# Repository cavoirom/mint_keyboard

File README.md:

# Mint Keyboard

Mint is an attempt to build 4x12 ortholinear keyboard with ***Weact STM32F411CEU6 Black Pill***. This repository include PCB design, plate design that anyone can build a Mint for themselves.

## Bill of materials

| Name                                 | Quantities | Ref | Description                                                |
|--------------------------------------|------------|-----|------------------------------------------------------------|
| Weact STM32F411CEU6 Black Pill       | 1          |     | Keyboard controller                                        |
| 1N4148 Diode                         | 47         |     |                                                            |
| Kailh Hotswap Socket                 | 44         |     |                                                            |
| Mill-Max sockets 0305                | 6          |     | 3 sockets above the controller could not use Kailh socket. |

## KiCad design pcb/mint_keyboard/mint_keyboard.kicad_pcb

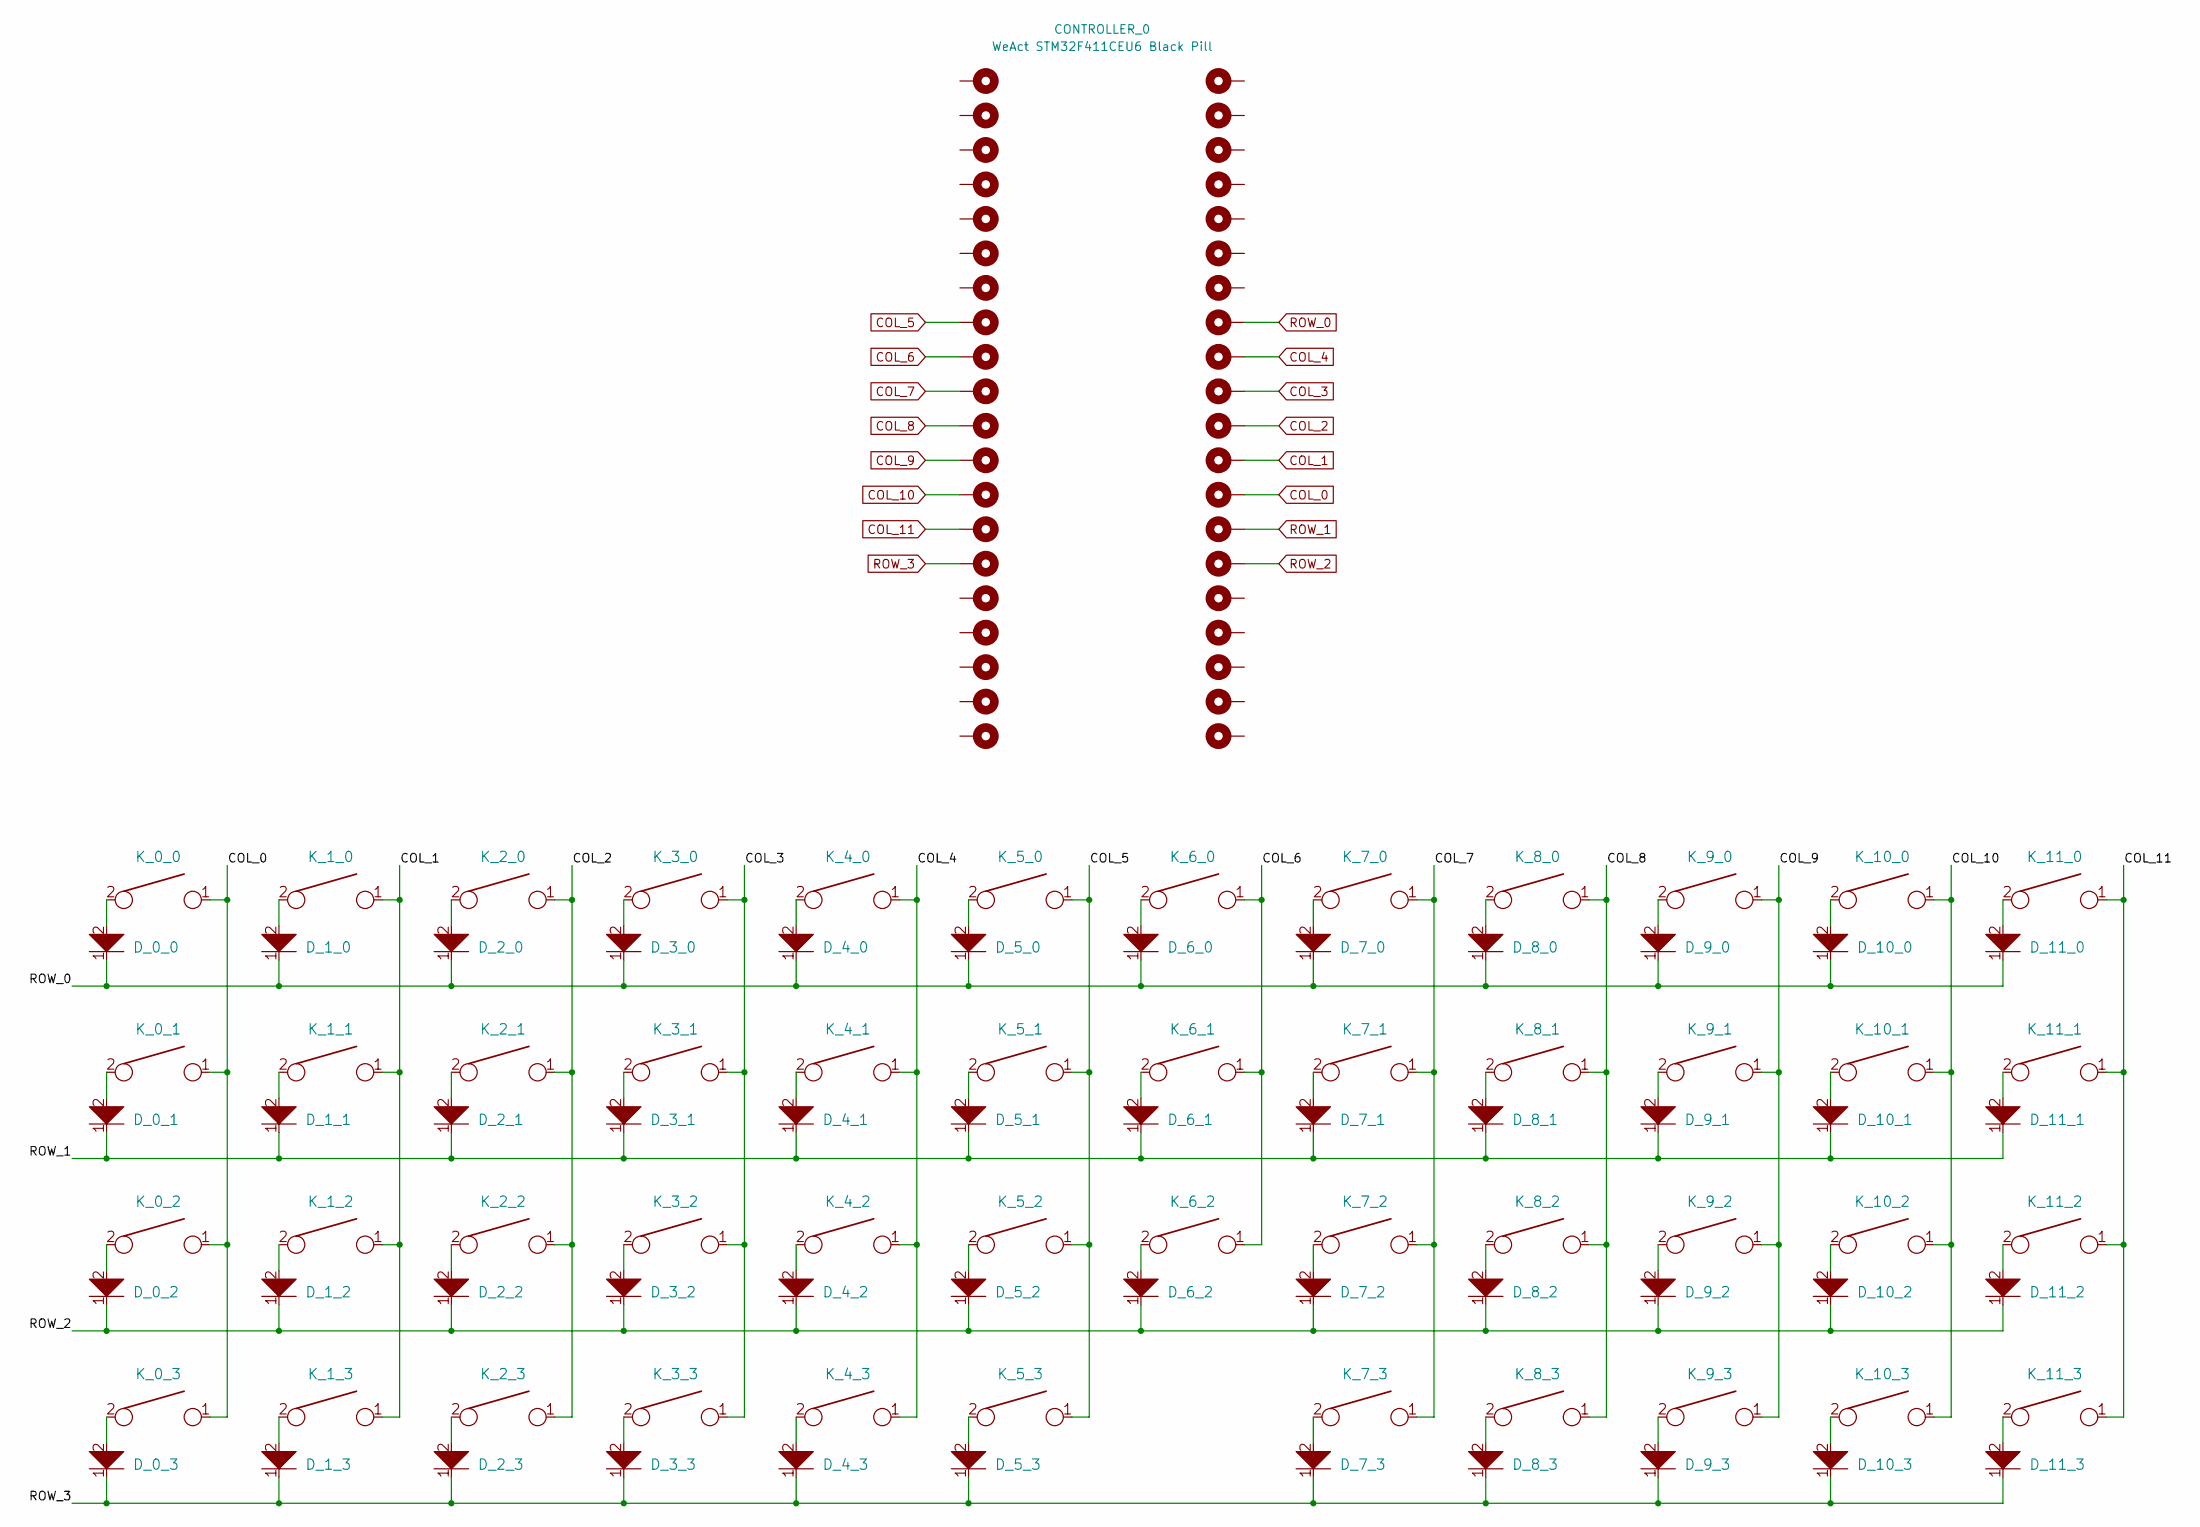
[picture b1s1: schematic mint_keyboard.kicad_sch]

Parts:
CONTROLLER_0: WeAct STM32F411CEU6 Black Pill; WeAct_STM32F411CEU6_Black_Pill_v3
D_0_0, D_0_1, D_0_2, D_0_3, D_1_0, D_1_1, D_1_2, D_1_3, D_2_0, D_2_1, D_2_2, D_2_3, D_3_0, D_3_1, D_3_2, D_3_3, D_4_0, D_4_1, D_4_2, D_4_3, D_5_0, D_5_1, D_5_2, D_5_3, D_6_0, D_6_1, D_6_2, D_7_0, D_7_1, D_7_2, D_7_3, D_8_0, D_8_1, D_8_2, D_8_3, D_9_0, D_9_1, D_9_2, D_9_3, D_10_0, D_10_1, D_10_2, D_10_3, D_11_0, D_11_1, D_11_2, D_11_3: D; D_DO-35_SOD27_P7.62mm_Horizontal
K_0_0: TAB; Kailh_socket_MX_padding
K_0_1, K_0_2, K_0_3, K_1_1, K_1_2, K_1_3, K_2_1, K_2_2, K_2_3, K_3_1, K_3_2, K_3_3, K_4_3, K_5_1, K_5_2, K_5_3, K_6_1, K_6_2, K_7_1, K_7_2, K_7_3, K_8_1, K_8_2, K_8_3, K_9_1, K_9_2, K_9_3, K_10_1, K_10_2, K_10_3, K_11_1, K_11_2, K_11_3: KEYSW; Kailh_socket_MX_padding
K_1_0: QUOTE; Kailh_socket_MX_padding
K_2_0: COMMA; Kailh_socket_MX_padding
K_3_0: PERIOD; Kailh_socket_MX_padding
K_4_0: P; SW_MX_padding
K_4_1, K_4_2: KEYSW; SW_MX_padding
K_5_0: Y; Kailh_socket_MX_padding
K_6_0: F; Kailh_socket_MX_padding
K_7_0: G; Kailh_socket_MX_padding
K_8_0: C; Kailh_socket_MX_padding
K_9_0: R; Kailh_socket_MX_padding
K_10_0: L; Kailh_socket_MX_padding
K_11_0: BACKSPACE; Kailh_socket_MX_padding

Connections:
COL_0: CONTROLLER_0.33 (A2), K_0_0.1, K_0_1.1, K_0_2.1, K_0_3.1
COL_1: CONTROLLER_0.32 (A3), K_1_0.1, K_1_1.1, K_1_2.1, K_1_3.1
COL_2: CONTROLLER_0.31 (A4), K_2_0.1, K_2_1.1, K_2_2.1, K_2_3.1
COL_3: CONTROLLER_0.30 (A5), K_3_0.1, K_3_1.1, K_3_2.1, K_3_3.1
COL_4: CONTROLLER_0.29 (A6), K_4_0.1, K_4_1.1, K_4_2.1, K_4_3.1
COL_5: CONTROLLER_0.8 (A11), K_5_0.1, K_5_1.1, K_5_2.1, K_5_3.1
COL_6: CONTROLLER_0.9 (A12), K_6_0.1, K_6_1.1, K_6_2.1
COL_7: CONTROLLER_0.10 (A15), K_7_0.1, K_7_1.1, K_7_2.1, K_7_3.1
COL_8: CONTROLLER_0.11 (B3), K_8_0.1, K_8_1.1, K_8_2.1, K_8_3.1
COL_9: CONTROLLER_0.12 (B4), K_9_0.1, K_9_1.1, K_9_2.1, K_9_3.1
COL_10: CONTROLLER_0.13 (B5), K_10_0.1, K_10_1.1, K_10_2.1, K_10_3.1
COL_11: CONTROLLER_0.14 (B6), K_11_0.1, K_11_1.1, K_11_2.1, K_11_3.1
unnamed: D_0_0.2, K_0_0.2
unnamed: D_0_1.2, K_0_1.2
unnamed: D_0_2.2, K_0_2.2
unnamed: D_0_3.2, K_0_3.2
unnamed: D_1_0.2, K_1_0.2
unnamed: D_1_1.2, K_1_1.2
unnamed: D_1_2.2, K_1_2.2
unnamed: D_1_3.2, K_1_3.2
unnamed: D_2_0.2, K_2_0.2
unnamed: D_2_1.2, K_2_1.2
unnamed: D_2_2.2, K_2_2.2
unnamed: D_2_3.2, K_2_3.2
unnamed: D_3_0.2, K_3_0.2
unnamed: D_3_1.2, K_3_1.2
unnamed: D_3_2.2, K_3_2.2
unnamed: D_3_3.2, K_3_3.2
unnamed: D_4_0.2, K_4_0.2
unnamed: D_4_1.2, K_4_1.2
unnamed: D_4_2.2, K_4_2.2
unnamed: D_4_3.2, K_4_3.2
unnamed: D_5_0.2, K_5_0.2
unnamed: D_5_1.2, K_5_1.2
unnamed: D_5_2.2, K_5_2.2
unnamed: D_5_3.2, K_5_3.2
unnamed: D_6_0.2, K_6_0.2
unnamed: D_6_1.2, K_6_1.2
unnamed: D_6_2.2, K_6_2.2
unnamed: D_7_0.2, K_7_0.2
unnamed: D_7_1.2, K_7_1.2
unnamed: D_7_2.2, K_7_2.2
unnamed: D_7_3.2, K_7_3.2
unnamed: D_8_0.2, K_8_0.2
unnamed: D_8_1.2, K_8_1.2
unnamed: D_8_2.2, K_8_2.2
unnamed: D_8_3.2, K_8_3.2
unnamed: D_9_0.2, K_9_0.2
unnamed: D_9_1.2, K_9_1.2
unnamed: D_9_2.2, K_9_2.2
unnamed: D_9_3.2, K_9_3.2
unnamed: D_10_0.2, K_10_0.2
unnamed: D_10_1.2, K_10_1.2
unnamed: D_10_2.2, K_10_2.2
unnamed: D_10_3.2, K_10_3.2
unnamed: D_11_0.2, K_11_0.2
unnamed: D_11_1.2, K_11_1.2
unnamed: D_11_2.2, K_11_2.2
unnamed: D_11_3.2, K_11_3.2
ROW_0: CONTROLLER_0.28 (A7), D_0_0.1, D_1_0.1, D_2_0.1, D_3_0.1, D_4_0.1, D_5_0.1, D_6_0.1, D_7_0.1, D_8_0.1, D_9_0.1, D_10_0.1, D_11_0.1
ROW_1: CONTROLLER_0.34 (A1), D_0_1.1, D_1_1.1, D_2_1.1, D_3_1.1, D_4_1.1, D_5_1.1, D_6_1.1, D_7_1.1, D_8_1.1, D_9_1.1, D_10_1.1, D_11_1.1
ROW_2: CONTROLLER_0.35 (A0), D_0_2.1, D_1_2.1, D_2_2.1, D_3_2.1, D_4_2.1, D_5_2.1, D_6_2.1, D_7_2.1, D_8_2.1, D_9_2.1, D_10_2.1, D_11_2.1
ROW_3: CONTROLLER_0.15 (B7), D_0_3.1, D_1_3.1, D_2_3.1, D_3_3.1, D_4_3.1, D_5_3.1, D_7_3.1, D_8_3.1, D_9_3.1, D_10_3.1, D_11_3.1

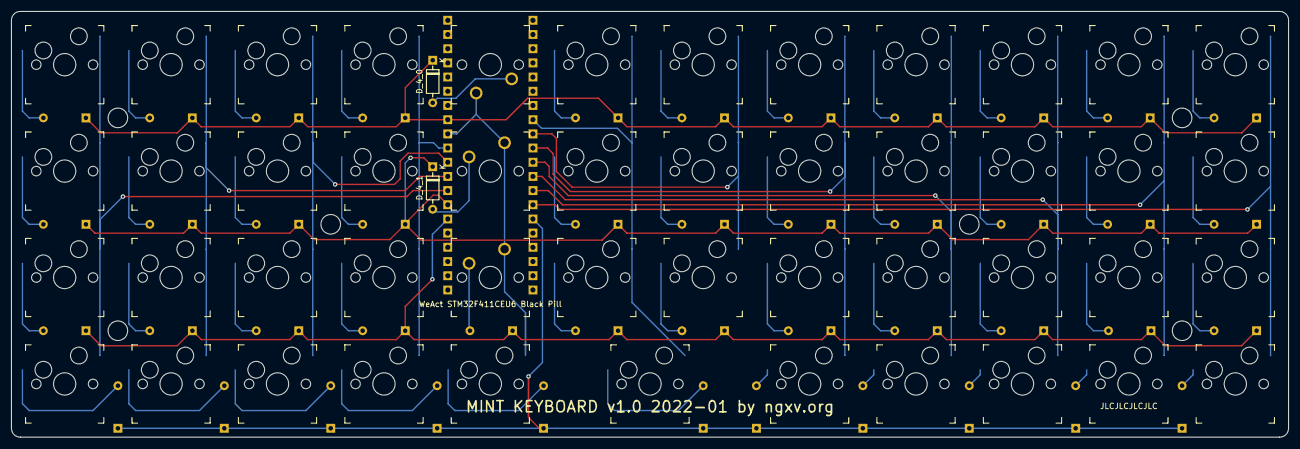
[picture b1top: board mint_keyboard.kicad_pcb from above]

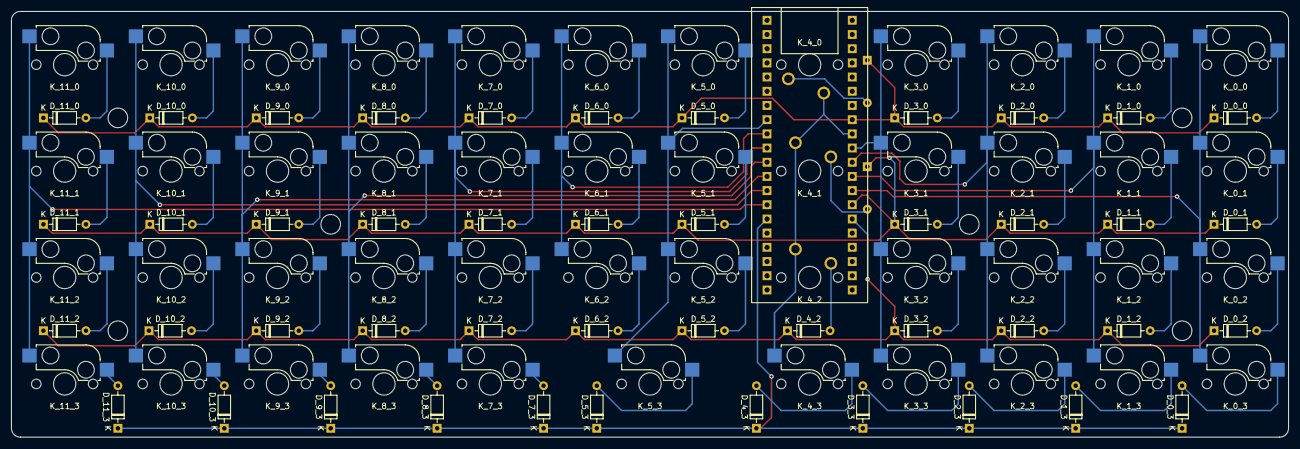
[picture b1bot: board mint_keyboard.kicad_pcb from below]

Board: 2 copper layers, 228.6 x 76.2 mm, 101 parts (46 on the bottom side), 63 nets.

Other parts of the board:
PLATE_HOLE_1, PLATE_HOLE_2, PLATE_HOLE_3, PLATE_HOLE_4, PLATE_HOLE_5, PLATE_HOLE_6: MountingHole_3.5mm

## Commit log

2022-02-27 Added README.md anh .gitignore.
2022-02-27 Added Mint Keyboard v1.0 PCB.
2022-02-27 Added Mint top/bottom plate.
2022-08-22 Added bill of materials to README.md
2022-08-22 Update bill of materials table with 1N4148 Diode, Kailh Hotswap Socket, Mill-Max sockets 0305.
